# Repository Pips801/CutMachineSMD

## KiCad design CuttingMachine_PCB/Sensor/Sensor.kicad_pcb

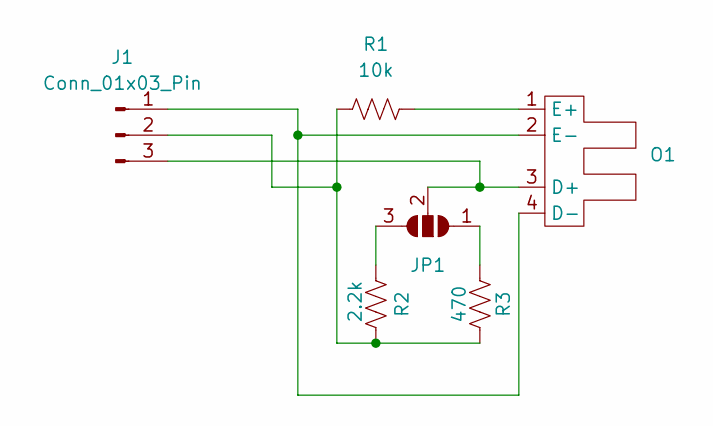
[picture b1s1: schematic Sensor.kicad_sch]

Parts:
J1: Conn_01x03_Pin; PinHeader_1x03_P2.54mm_Vertical
JP1: SolderJumper_3_Open; SolderJumper-3_P2.0mm_Open_TrianglePad1.0x1.5mm_NumberLabels
O1: MOC7811
R1: 10k; R_1206_3216Metric_Pad1.30x1.75mm_HandSolder
R2: 2.2k; R_1206_3216Metric_Pad1.30x1.75mm_HandSolder
R3: 470; R_1206_3216Metric_Pad1.30x1.75mm_HandSolder

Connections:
unnamed: J1.1, O1.2 (E-), O1.4 (D-)
unnamed: J1.2, R1.1, R2.1, R3.1
unnamed: J1.3, JP1.2 (C), O1.3 (D+)
unnamed: JP1.1 (A), R3.2
unnamed: JP1.3 (B), R2.2
unnamed: O1.1 (E+), R1.2

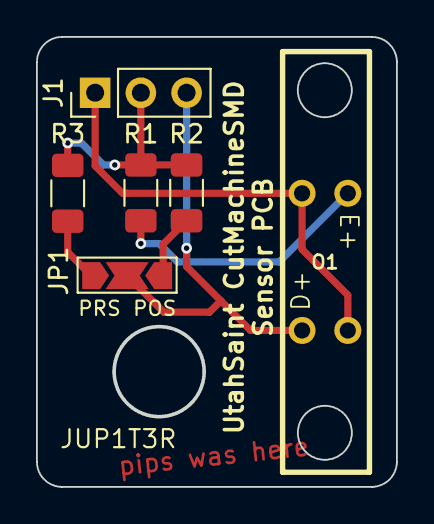
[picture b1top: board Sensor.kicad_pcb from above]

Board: 2 copper layers, 20.0 x 25.0 mm, 6 parts (0 on the bottom side), 6 nets.

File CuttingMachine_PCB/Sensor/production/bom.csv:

Designator,Footprint,Quantity,Value,LCSC Part #
J1,PinHeader_1x03_P2.54mm_Vertical,1,Conn_01x03_Pin,
O1,MOC7811,1,~,
R1,1206,1,10k,
R2,1206,1,2.2k,
R3,1206,1,470,

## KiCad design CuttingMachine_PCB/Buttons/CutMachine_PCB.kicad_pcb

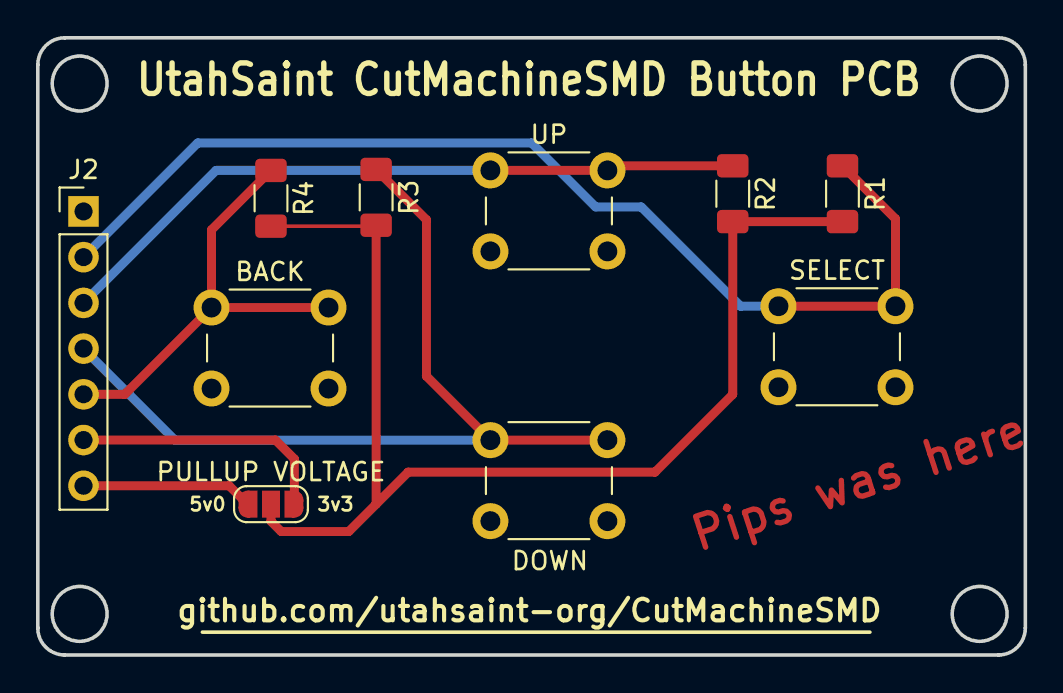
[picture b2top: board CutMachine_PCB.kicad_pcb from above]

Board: 2 copper layers, 54.9 x 34.3 mm, 10 parts (0 on the bottom side), 8 nets.

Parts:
BACK: BACK; SW_PUSH_6mm_H4.3mm
J2: Conn_01x07_Pin; PinHeader_1x07_P2.54mm_Vertical
PULLUP VOLTAGE: SolderJumper_3_Open; SolderJumper-3_P1.3mm_Open_RoundedPad1.0x1.5mm_NumberLabels
R1, R2, R3, R4: PULLUP; R_1206_3216Metric_Pad1.30x1.75mm_HandSolder
SELECT: SELECT; SW_PUSH_6mm_H4.3mm
SW3: DOWN; SW_PUSH_6mm_H4.3mm
UP: UP; SW_PUSH_6mm_H4.3mm

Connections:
+3.3V: J2.6, PULLUP VOLTAGE.3 (B)
+5V: J2.7, PULLUP VOLTAGE.1 (A)
GND: BACK.2, J2.1, SELECT.2, SW3.2, UP.2
unnamed: J2.2, R1.1, SELECT.1
unnamed: J2.3, R2.1, UP.1
unnamed: J2.4, R3.1, SW3.1
unnamed: BACK.1, J2.5, R4.1
unnamed: PULLUP VOLTAGE.2 (C), R1.2, R2.2, R3.2, R4.2

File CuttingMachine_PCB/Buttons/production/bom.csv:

Designator,Footprint,Quantity,Value,LCSC Part #
BACK,SW_PUSH_6mm_H4.3mm,1,BACK,
J2,PinHeader_1x07_P2.54mm_Vertical,1,Conn_01x07_Pin,
"R1, R2, R3, R4",1206,4,PULLUP,
SELECT,SW_PUSH_6mm_H4.3mm,1,SELECT,
SW3,SW_PUSH_6mm_H4.3mm,1,DOWN,
UP,SW_PUSH_6mm_H4.3mm,1,UP,

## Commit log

2024-09-12 Update fp-info-cache
2024-09-12 Settings Adjustments
    Changed the settings to increment by 10s after 10 selected. Basically an efficiency update.
